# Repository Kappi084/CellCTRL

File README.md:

# CellCTRL
Ist ein modulares System, um ein kleines Produktionssystem aufbauen zu können.

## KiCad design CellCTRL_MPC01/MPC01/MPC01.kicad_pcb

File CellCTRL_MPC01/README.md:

# CellCTRL Electric

Das MPC01 Board wurde für den Manipulator der KTLA ausgelegt.

Aktoren Anschluss:
4x (TMC2009) Stepper Motor
2x Servo Motor

Sensorik:
3x Endschalter (XYZ)

Bus Systeme:
I2C (Für Test Controller im Test Betrieb) (Ausgeführt über SDA und SCL) Nur bei UNO R3 vorhanden
RS485 Kommunikation einzelner Module zu einer Fertigungskette

## 🛠 Skills
Löten, Basic Bauteilkunde, 

## MPC01

#### Usage:
Der MPC01 Controller ist für die Steuerung von 3 Stepper Motoren (TMC2209 Treiber) mit jeweils einem Endschlater designt. Es können über I2C noch weitere Module mitangesteuert werden, wie den MPC-Servo und MPC-Status. Über RS485 sollen mit den anderen Module der Produktionsstraße kommuniziert werden können. (Error Übergabe, Befehle, etc.) Mit der Anbindung von PDNUart, ist es möglich den Motor nach dem Einschalten zu konfigurieren.

#### Features:
3x Steppermotor
3x Endschalter 
1x Notaussignal (Enable_Stepper) (NC)
1x I2C
1x RS485

| Connector | Arduino Pin     | Description                |
| :-------- | :------- | :------------------------- |
| `Endstop Z` | `A0` | NC_Endstop |
| `Endstop Y` | `A1` | NC_Endstop |
| `Endstop X` | `A2` | NC_Endstop |
| `RS485_DE/RE` | `A3` | RS485 |
| `SDA/SCL` | `A4` | I2C |
| `SDA/SCL` | `A5` | I2C |
| `DIR 3` | `D2` | Motor 3 |
| `STEP 3` | `D3` | Motor 3 |
| `DIR 2` | `D4` | Motor 2 |
| `STEP 2` | `D5` | Motor 2 |
| `DIR 1` | `D6` | Motor 1 |
| `STEP 1` | `D7` | Motor 1 |
| `TX` | `D8` | PDNUart StepperMotor |
| `RX` | `D9` | PDNUart StepperMotor |
| `RS485 TX` | `D10` | RS485 |
| `RS485 RX` | `D11` | RS485 |
| `PGOOD` | `D12` | Power OK 5V |
| `Enable` | `D13` | Enable Stepper Motor (Notaus) |

### ⚠️ Notes
Um PDNUART verwenden zu können, müssen mit Jumper bei MS1 und MS2 noch die richtigen Adressen eingestellt werden.

## MPC_Servo

#### Usage:
Der MPC_Servo Controller wird über I2C angesteuert, und kann entweder zwei Servos oder einen Servo und einem Endschalter betrieben werden.

#### Features:
1x Servo
1x Servo/Endschalter

#### Schnittstellenbescreibung:

| Address | Name        | R/W | Description              |
|--------|------------|-----|--------------------------|
| 0x00   | Mode     | R/W   | 0=Dual Servo, 1=Servo+Endstop   |
| 0x01   | Servo1 POS    | R/W | Servo 1 Zielwinkel  (0-180)         |
| 0x02   | Servo2 POS    | R/W | Servo 2 Zielwinkel  (nur Mode 0)         |
| 0x03   | Servo1 CUR   | R   | Servo 1 aktueller Winkel        |
| 0x04   | Servo2 CUR   | R   | Servo 2 aktueller Winkel        |
| 0x05   | Endstop   | R   | Endstop 0=offen, 1=ausgeloest        |
| 0x06   | Home CMD   | W   | 1=Homing starten        |
| 0x07   | Home Status   | R   | 0=idle 1=running 2=done 3=error        |
| 0x08   | Status   | R   | bit0=alive        |
| 0x09   | FW Version   | R   | Firmware-Version        |

## MPC_Status

#### Usage:
Der MPC_Status Controller wird ebenfalls mit I2C gesteuert, und wirkt somit wie der Servo ein "Modul". Mit dem ist es möglich, den jeweiligen Status der Anlage anzuzeigen mithilfe von LEDs.

#### Features:
1x LED Statuslicht

| Color | Status     | Description                |
| :-------- | :------- | :------------------------- |
| Blau leuchtend | Boot | Bei hochfahren der Anlage |
| Blau blinkend | Homing | Beim Homen und Initialisieren der Anlage |
| Grün leuchtend | Ready | Die Anlage steht, aber ist Bereit für Befehle |
| Gelb leuchtend | Auto | Ist im Automatikbetrieb, und steht |
| Gelb blinkend | Manual | Ist im Manuelen Betrieb, und steht |
| Rot leuchtend | Moving | Die Anlage bewegt eine Achse etc. |
| Rot blinkend | EStop | Der Not Aus wurde betätigt, muss Quittiert werden! |
| Rot drehend | Error | Es liegt ein Fehler bei der Anlage an! (Quittierung notwendig) |

#### ⚙️ Configuration I2C_Status

- **I²C Address:** `0x3C`
- **Bus Speed:** Up to 400kHz (Fast Mode)
- **Addressing Mode:** 7-bit

#### 📋 Register Map I2C_Status

| Address | Name        | R/W | Description              |
|--------|------------|-----|--------------------------|
| 0x00   | STATUS     | R   | Device status register   |
| 0x01   | CONTROL    | R/W | Control settings         |
| 0x02   | TEMP_MSB   | R   | Temperature (MSB)        |
| 0x03   | TEMP_LSB   | R   | Temperature (LSB)        |

#### 🔄 Example
```cpp
// example code

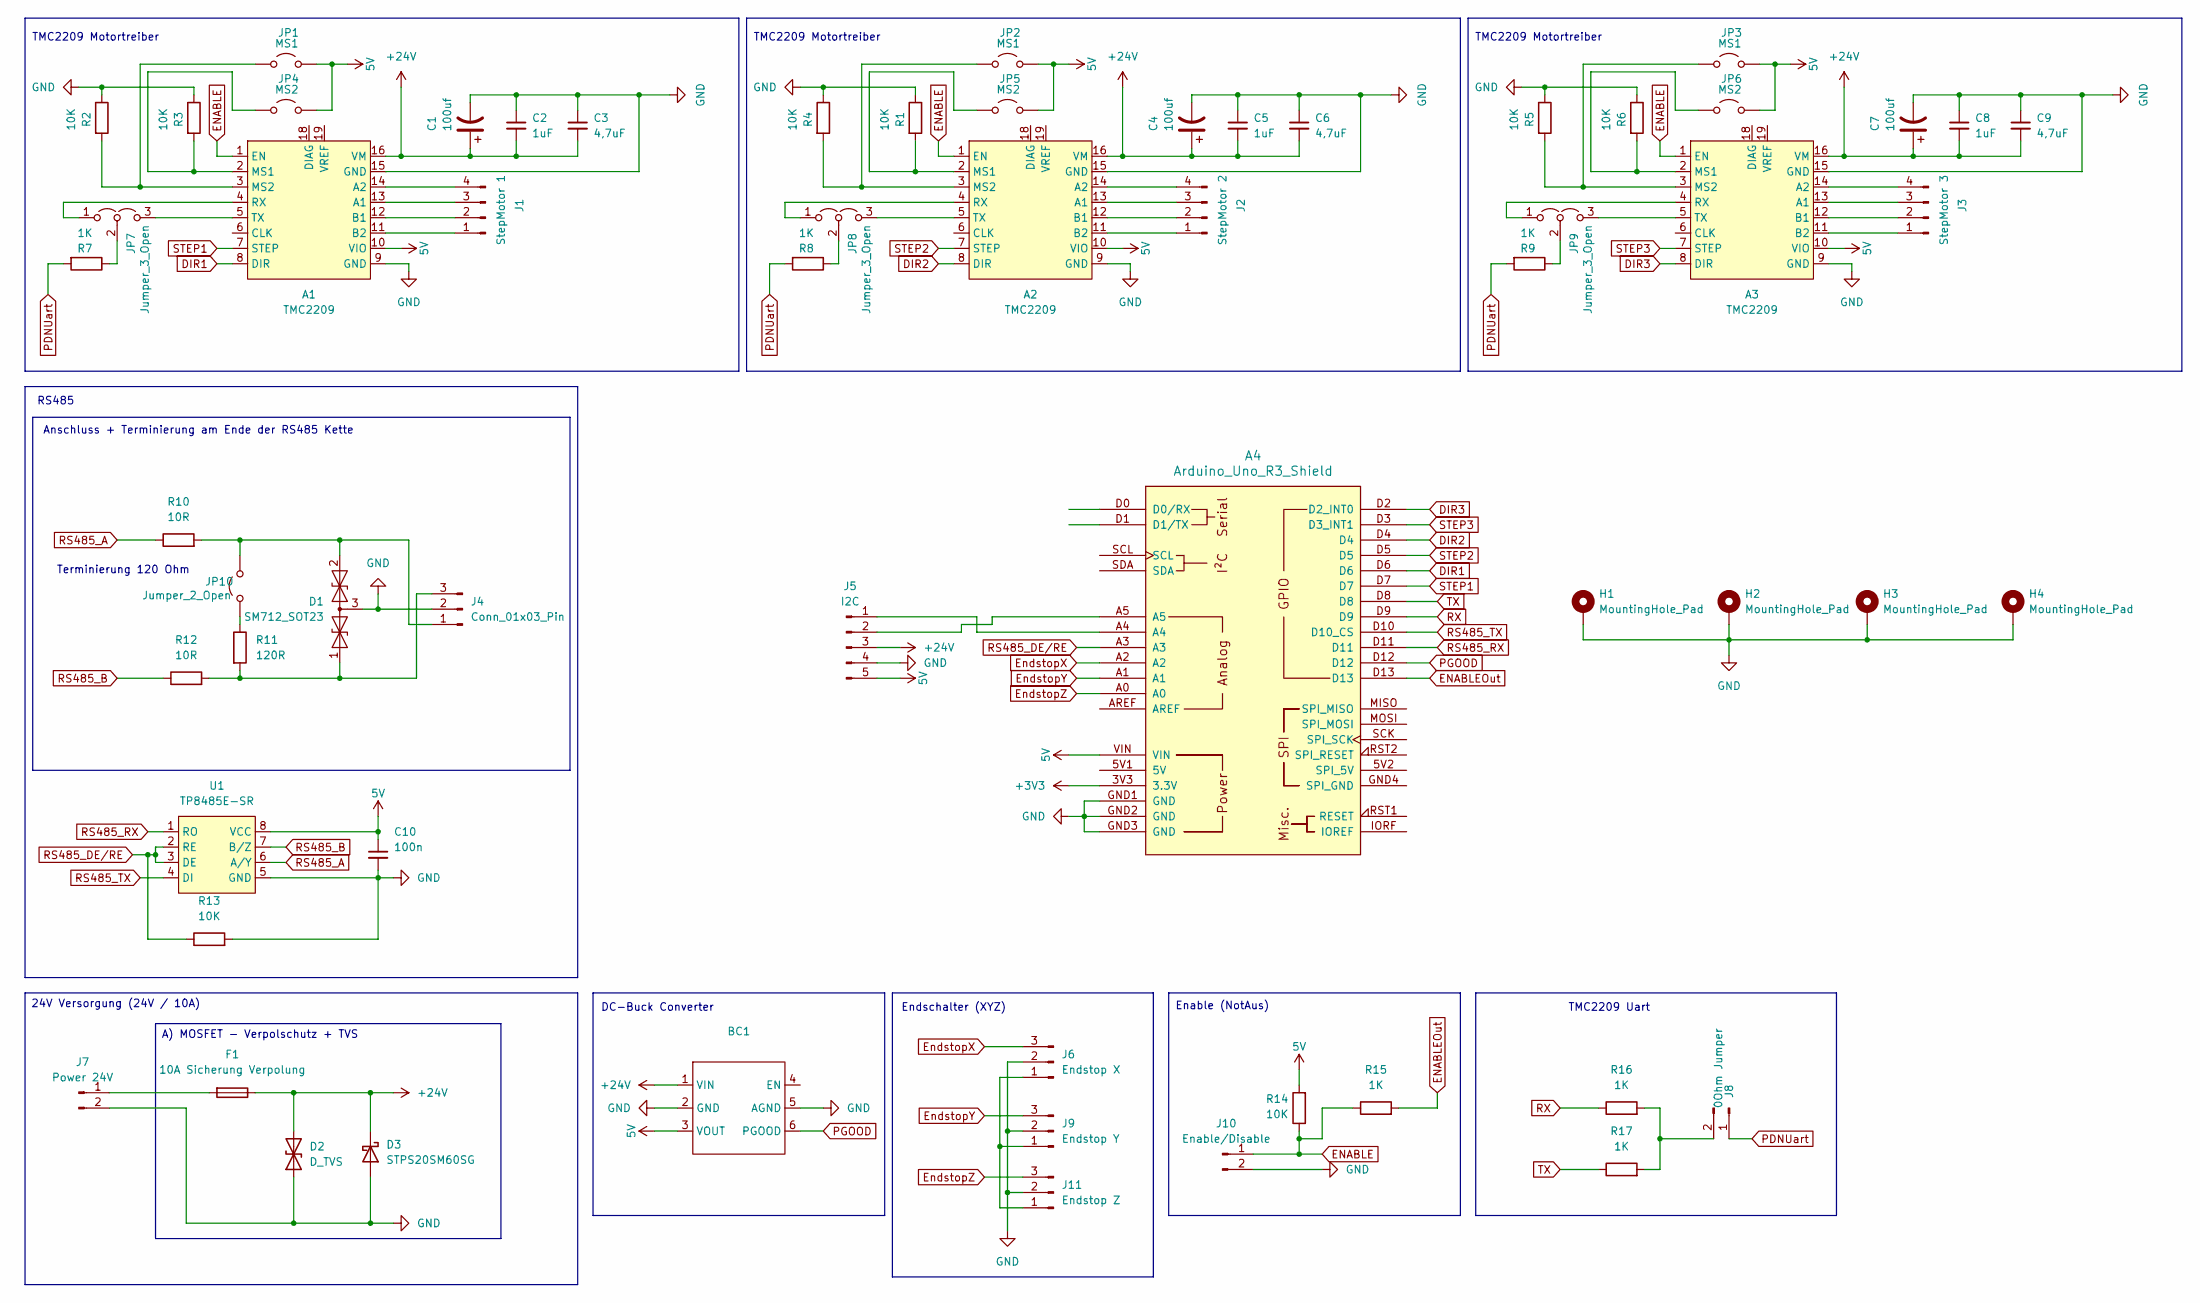
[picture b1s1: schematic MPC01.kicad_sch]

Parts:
A1, A2, A3: TMC2209
A4: Arduino_Uno_R3_Shield
BC1: DC-DC Step Down Buck Converter (6~24V to 5V16A)
C1, C4, C7: 100uf; CP_Elec_6.3x7.7
C2, C5, C8: 1uF; C_0805_2012Metric_Pad1.18x1.45mm_HandSolder; Voltage 1kV; Tolerance 100%
C3, C6, C9: 4,7uF; C_0805_2012Metric_Pad1.18x1.45mm_HandSolder; Voltage 1kV; Tolerance 100%
C10: 100n; C_0805_2012Metric_Pad1.18x1.45mm_HandSolder; Voltage 1kV; Tolerance 100%
D1: SM712_SOT23; SOT-23-3
D2: D_TVS; D_SMB_Handsoldering
D3: STPS20SM60SG; TO-263-2_TabPin2
F1: 10A Sicherung Verpolung; Fuseholder_Littelfuse_Nano2_157x
H1, H2, H3, H4: MountingHole_Pad; MountingHole_2.2mm_M2_DIN965_Pad
J1: StepMotor 1; JST_XH_B4B-XH-A_1x04_P2.50mm_Vertical
J2: StepMotor 2; JST_XH_B4B-XH-A_1x04_P2.50mm_Vertical
J3: StepMotor 3; JST_XH_B4B-XH-A_1x04_P2.50mm_Vertical
J4: Conn_01x03_Pin; PhoenixContact_MSTBA_2,5_3-G-5,08_1x03_P5.08mm_Horizontal
J5: I2C; JST_XH_B5B-XH-A_1x05_P2.50mm_Vertical
J6: Endstop X; JST_XH_B3B-XH-A_1x03_P2.50mm_Vertical
J7: Power 24V; TerminalBlock_WAGO_2601-1102_1x02_P3.50mm_Horizontal
J8: 0Ohm Jumper; PinHeader_1x02_P2.54mm_Vertical
J9: Endstop Y; JST_XH_B3B-XH-A_1x03_P2.50mm_Vertical
J10: Enable/Disable; JST_XH_B2B-XH-A_1x02_P2.50mm_Vertical
J11: Endstop Z; JST_XH_B3B-XH-A_1x03_P2.50mm_Vertical
JP1, JP2, JP3: MS1; PinHeader_1x02_P2.54mm_Vertical
JP4, JP5, JP6: MS2; PinHeader_1x02_P2.54mm_Vertical
JP7, JP8, JP9: Jumper_3_Open; Jumper_3_NO
JP10: Jumper_2_Open; SolderJumper-2_P1.3mm_Open_RoundedPad1.0x1.5mm
R1, R2, R3, R4, R5, R6, R13, R14: 10K; R_0805_2012Metric_Pad1.20x1.40mm_HandSolder
R7, R8, R9, R15, R16, R17: 1K; R_0805_2012Metric_Pad1.20x1.40mm_HandSolder
R10, R12: 10R; R_0805_2012Metric_Pad1.20x1.40mm_HandSolder
R11: 120R; R_0805_2012Metric_Pad1.20x1.40mm_HandSolder
U1: TP8485E-SR; SOP-8_3.76x4.96mm_P1.27mm

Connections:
5V: A1.10 (VIO), A2.10 (VIO), A3.10 (VIO), A4.VIN, BC1.3 (VOUT), C10.1, J5.5, JP1.2 (B), JP2.2 (B), JP3.2 (B), JP4.2 (B), JP5.2 (B), JP6.2 (B), R14.2, U1.8 (VCC)
+3V3: A4.3V3 (3.3V)
+24V: A1.16 (VM), A2.16 (VM), A3.16 (VM), BC1.1 (VIN), C1.1, C2.2, C3.2, C4.1, C5.2, C6.2, C7.1, C8.2, C9.2, D2.2 (A2), D3.1 (K), F1.1, J5.3
DIR1: A1.8 (DIR), A4.D6
DIR2: A2.8 (DIR), A4.D4
DIR3: A3.8 (DIR), A4.D2 (D2_INT0)
ENABLE: A1.1 (EN), A2.1 (EN), A3.1 (EN), J10.1, R14.1, R15.1
ENABLEOut: A4.D13, R15.2
EndstopX: A4.A2, J6.3
EndstopY: A4.A1, J9.3
EndstopZ: A4.A0, J11.3
GND: A1.9 (GND), A1.15 (GND), A2.9 (GND), A2.15 (GND), A3.9 (GND), A3.15 (GND), A4.GND1 (GND), A4.GND2 (GND), A4.GND3 (GND), BC1.2 (GND), BC1.5 (AGND), C1.2, C2.1, C3.1, C4.2, C5.1, C6.1, C7.2, C8.1, C9.1, C10.2, D1.3 (common), D2.1 (A1), D3.2 (A), H1.1, H2.1, H3.1, H4.1, J4.2, J5.4, J6.2, J7.2, J9.2, J10.2, J11.2, R1.1, R2.1, R3.1, R4.1, R5.1, R6.1, R13.2, U1.5 (GND)
unnamed: A1.13 (A1), J1.3
unnamed: A1.14 (A2), J1.4
unnamed: A1.12 (B1), J1.2
unnamed: A1.11 (B2), J1.1
unnamed: A1.2 (MS1), JP4.1 (A), R3.2
unnamed: A1.3 (MS2), JP1.1 (A), R2.2
unnamed: A1.4 (RX), JP7.1 (A)
unnamed: A1.5 (TX), JP7.3 (B)
unnamed: A2.13 (A1), J2.3
unnamed: A2.14 (A2), J2.4
unnamed: A2.12 (B1), J2.2
unnamed: A2.11 (B2), J2.1
unnamed: A2.2 (MS1), JP5.1 (A), R1.2
unnamed: A2.3 (MS2), JP2.1 (A), R4.2
unnamed: A2.4 (RX), JP8.1 (A)
unnamed: A2.5 (TX), JP8.3 (B)
unnamed: A3.13 (A1), J3.3
unnamed: A3.14 (A2), J3.4
unnamed: A3.12 (B1), J3.2
unnamed: A3.11 (B2), J3.1
unnamed: A3.2 (MS1), JP6.1 (A), R6.2
unnamed: A3.3 (MS2), JP3.1 (A), R5.2
unnamed: A3.4 (RX), JP9.1 (A)
unnamed: A3.5 (TX), JP9.3 (B)
unnamed: D1.1 (A1), J4.3, R11.2, R12.2
unnamed: D1.2 (A2), J4.1, JP10.2 (B), R10.2
unnamed: A4.A4, J5.1
unnamed: A4.A5, J5.2
unnamed: F1.2, J7.1
unnamed: J8.2, R16.2, R17.2
unnamed: J6.1, J9.1, J11.1
unnamed: JP7.2 (C), R7.1
unnamed: JP8.2 (C), R8.1
unnamed: JP9.2 (C), R9.1
unnamed: JP10.1 (A), R11.1
PDNUart: J8.1, R7.2, R8.2, R9.2
PGOOD: A4.D12, BC1.6 (PGOOD)
RS485_A: R10.1, U1.6 (A/Y)
RS485_B: R12.1, U1.7 (B/Z)
RS485_DE/RE: A4.A3, R13.1, U1.2 (RE), U1.3 (DE)
RS485_RX: A4.D11, U1.1 (RO)
RS485_TX: A4.D10 (D10_CS), U1.4 (DI)
RX: A4.D9, R16.1
STEP1: A1.7 (STEP), A4.D7
STEP2: A2.7 (STEP), A4.D5
STEP3: A3.7 (STEP), A4.D3 (D3_INT1)
TX: A4.D8, R17.1

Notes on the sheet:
Terminierung 120 Ohm
Enable (NotAus)
TMC2209 Motortreiber
RS485
Endschalter (XYZ)
Anschluss + Terminierung am Ende der RS485 Kette
DC-Buck Converter
TMC2209 Uart
24V Versorgung (24V / 10A)
A) MOSFET - Verpolschutz + TVS

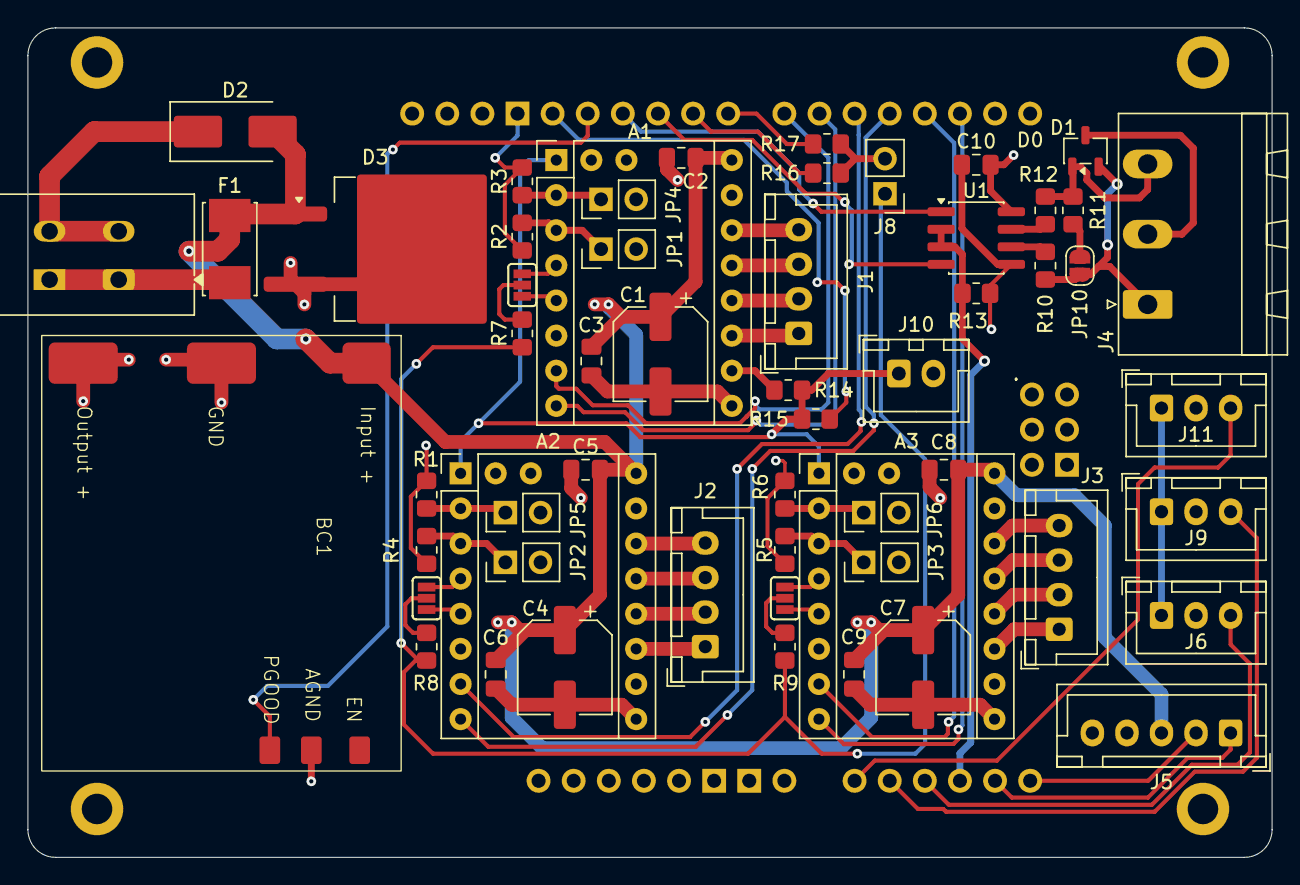
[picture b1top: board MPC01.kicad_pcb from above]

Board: 4 copper layers, 90.0 x 60.0 mm, 62 parts (0 on the bottom side), 58 nets.

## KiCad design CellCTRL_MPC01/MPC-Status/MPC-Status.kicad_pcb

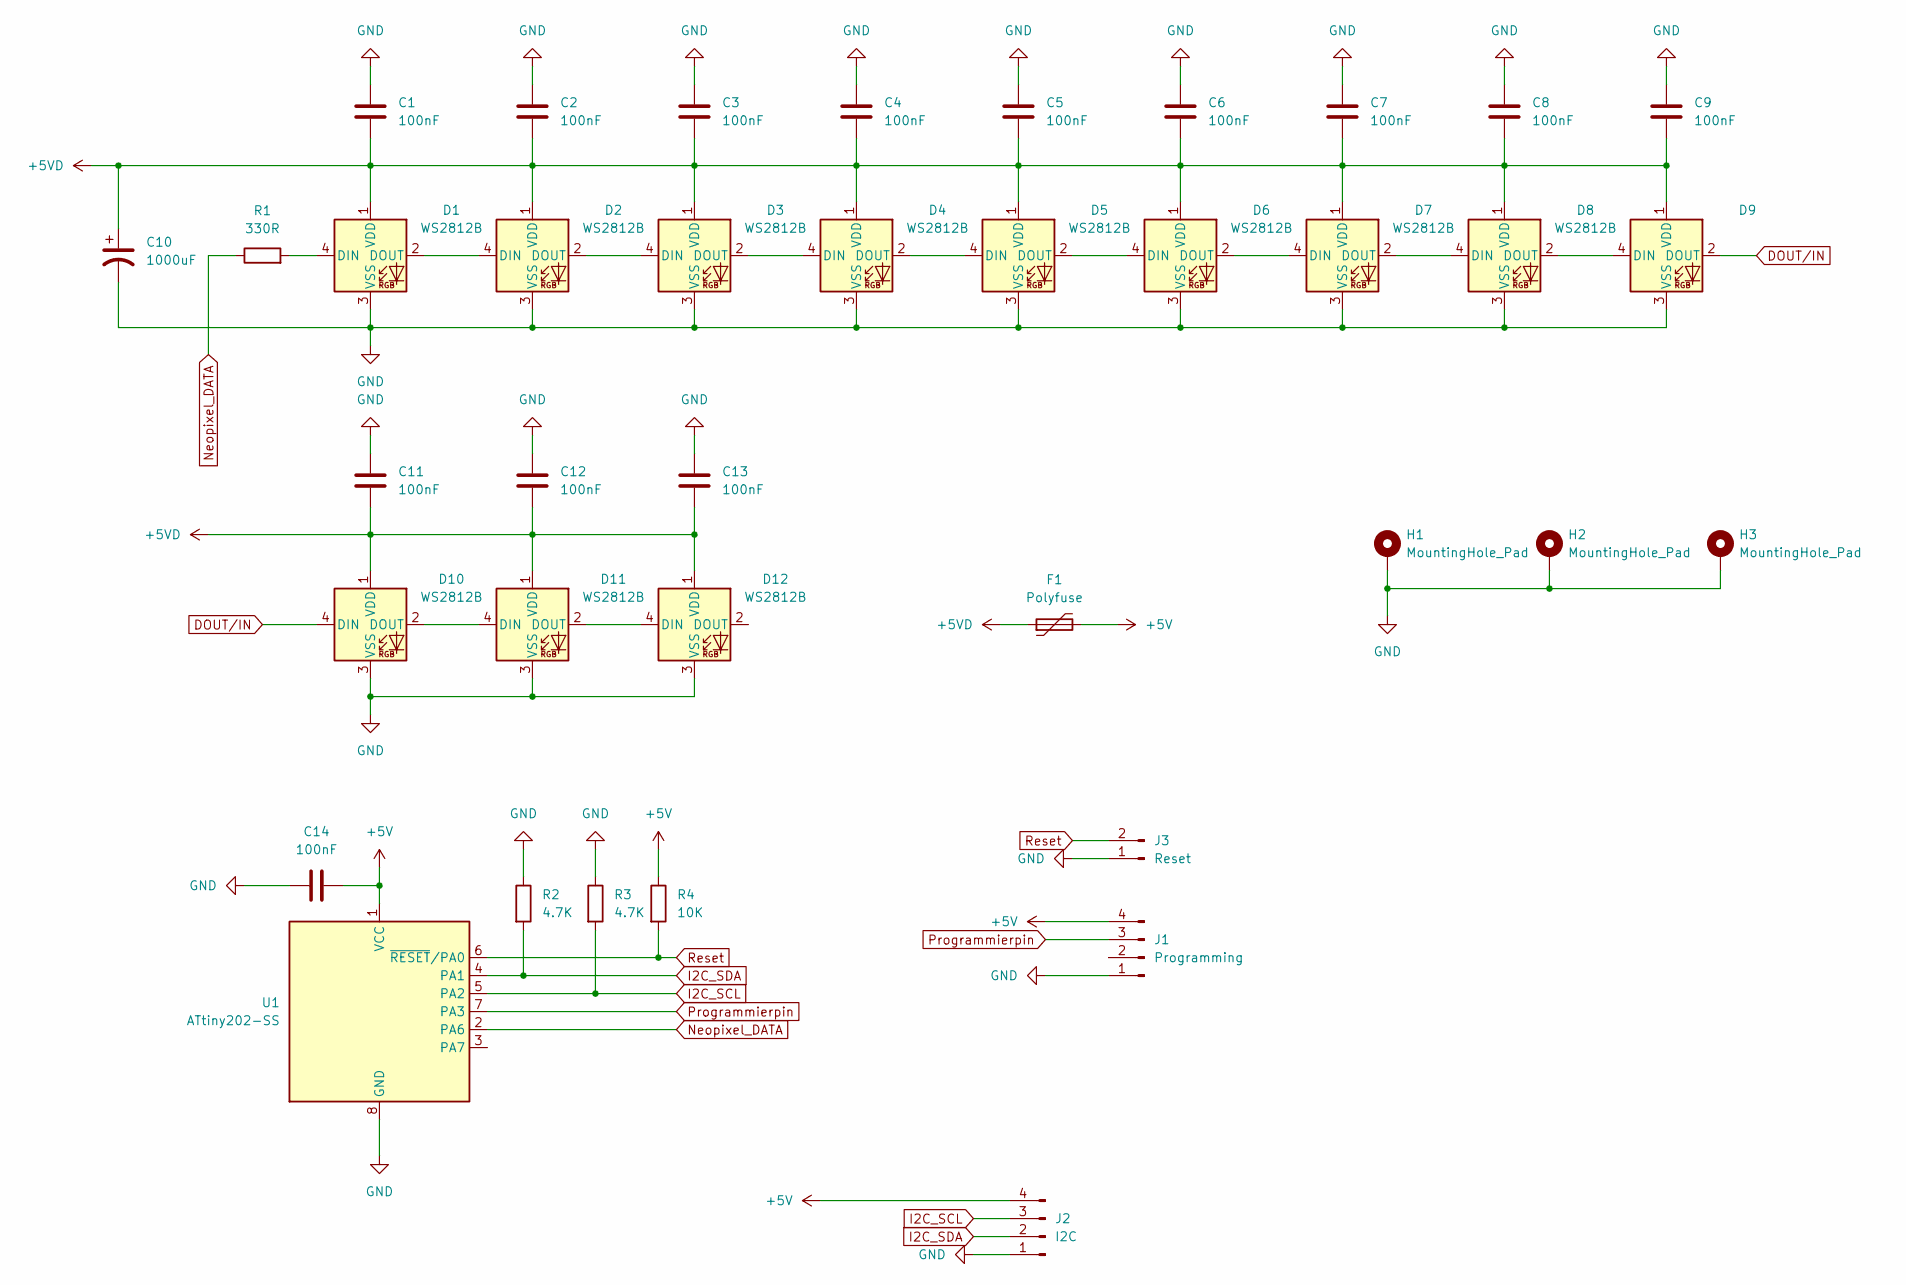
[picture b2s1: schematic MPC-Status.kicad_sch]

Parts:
C1, C2, C3, C4, C5, C6, C7, C8, C9, C11, C12, C13, C14: 100nF; C_0805_2012Metric_Pad1.18x1.45mm_HandSolder
C10: 1000uF; CP_Elec_6.3x5.4
D1, D2, D3, D4, D5, D6, D7, D8, D9, D10, D11, D12: WS2812B; LED_WS2812B_PLCC4_5.0x5.0mm_P3.2mm
F1: Polyfuse; Fuse_0805_2012Metric_Pad1.15x1.40mm_HandSolder
H1, H2, H3: MountingHole_Pad; MountingHole_3.2mm_M3_DIN965_Pad
J1: Programming; PinHeader_1x04_P2.54mm_Vertical
J2: I2C; JST_XH_B4B-XH-A_1x04_P2.50mm_Vertical
J3: Reset; PinHeader_1x02_P2.54mm_Vertical
R1: 330R; R_0805_2012Metric_Pad1.20x1.40mm_HandSolder
R2, R3: 4.7K; R_0805_2012Metric_Pad1.20x1.40mm_HandSolder
R4: 10K; R_0805_2012Metric_Pad1.20x1.40mm_HandSolder
U1: ATtiny202-SS; SOIC-8_3.9x4.9mm_P1.27mm

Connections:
+5V: C14.2, F1.2, J1.4, J2.4, R4.1, U1.1 (VCC)
+5VD: C1.1, C2.1, C3.1, C4.1, C5.1, C6.1, C7.1, C8.1, C9.1, C10.1, C11.1, C12.1, C13.1, D1.1 (VDD), D2.1 (VDD), D3.1 (VDD), D4.1 (VDD), D5.1 (VDD), D6.1 (VDD), D7.1 (VDD), D8.1 (VDD), D9.1 (VDD), D10.1 (VDD), D11.1 (VDD), D12.1 (VDD), F1.1
DOUT/IN: D9.2 (DOUT), D10.4 (DIN)
GND: C1.2, C2.2, C3.2, C4.2, C5.2, C6.2, C7.2, C8.2, C9.2, C10.2, C11.2, C12.2, C13.2, C14.1, D1.3 (VSS), D2.3 (VSS), D3.3 (VSS), D4.3 (VSS), D5.3 (VSS), D6.3 (VSS), D7.3 (VSS), D8.3 (VSS), D9.3 (VSS), D10.3 (VSS), D11.3 (VSS), D12.3 (VSS), H1.1, H2.1, H3.1, J1.1, J2.1, J3.1, R2.1, R3.1, U1.8 (GND)
I2C_SCL: J2.3, R3.2, U1.5 (PA2)
I2C_SDA: J2.2, R2.2, U1.4 (PA1)
Neopixel_DATA: R1.1, U1.2 (PA6)
unnamed: D1.4 (DIN), R1.2
unnamed: D1.2 (DOUT), D2.4 (DIN)
unnamed: D2.2 (DOUT), D3.4 (DIN)
unnamed: D3.2 (DOUT), D4.4 (DIN)
unnamed: D4.2 (DOUT), D5.4 (DIN)
unnamed: D5.2 (DOUT), D6.4 (DIN)
unnamed: D6.2 (DOUT), D7.4 (DIN)
unnamed: D7.2 (DOUT), D8.4 (DIN)
unnamed: D8.2 (DOUT), D9.4 (DIN)
unnamed: D10.2 (DOUT), D11.4 (DIN)
unnamed: D11.2 (DOUT), D12.4 (DIN)
Programmierpin: J1.3, U1.7 (PA3)
Reset: J3.2, R4.2, U1.6 (~RESET/PA0)

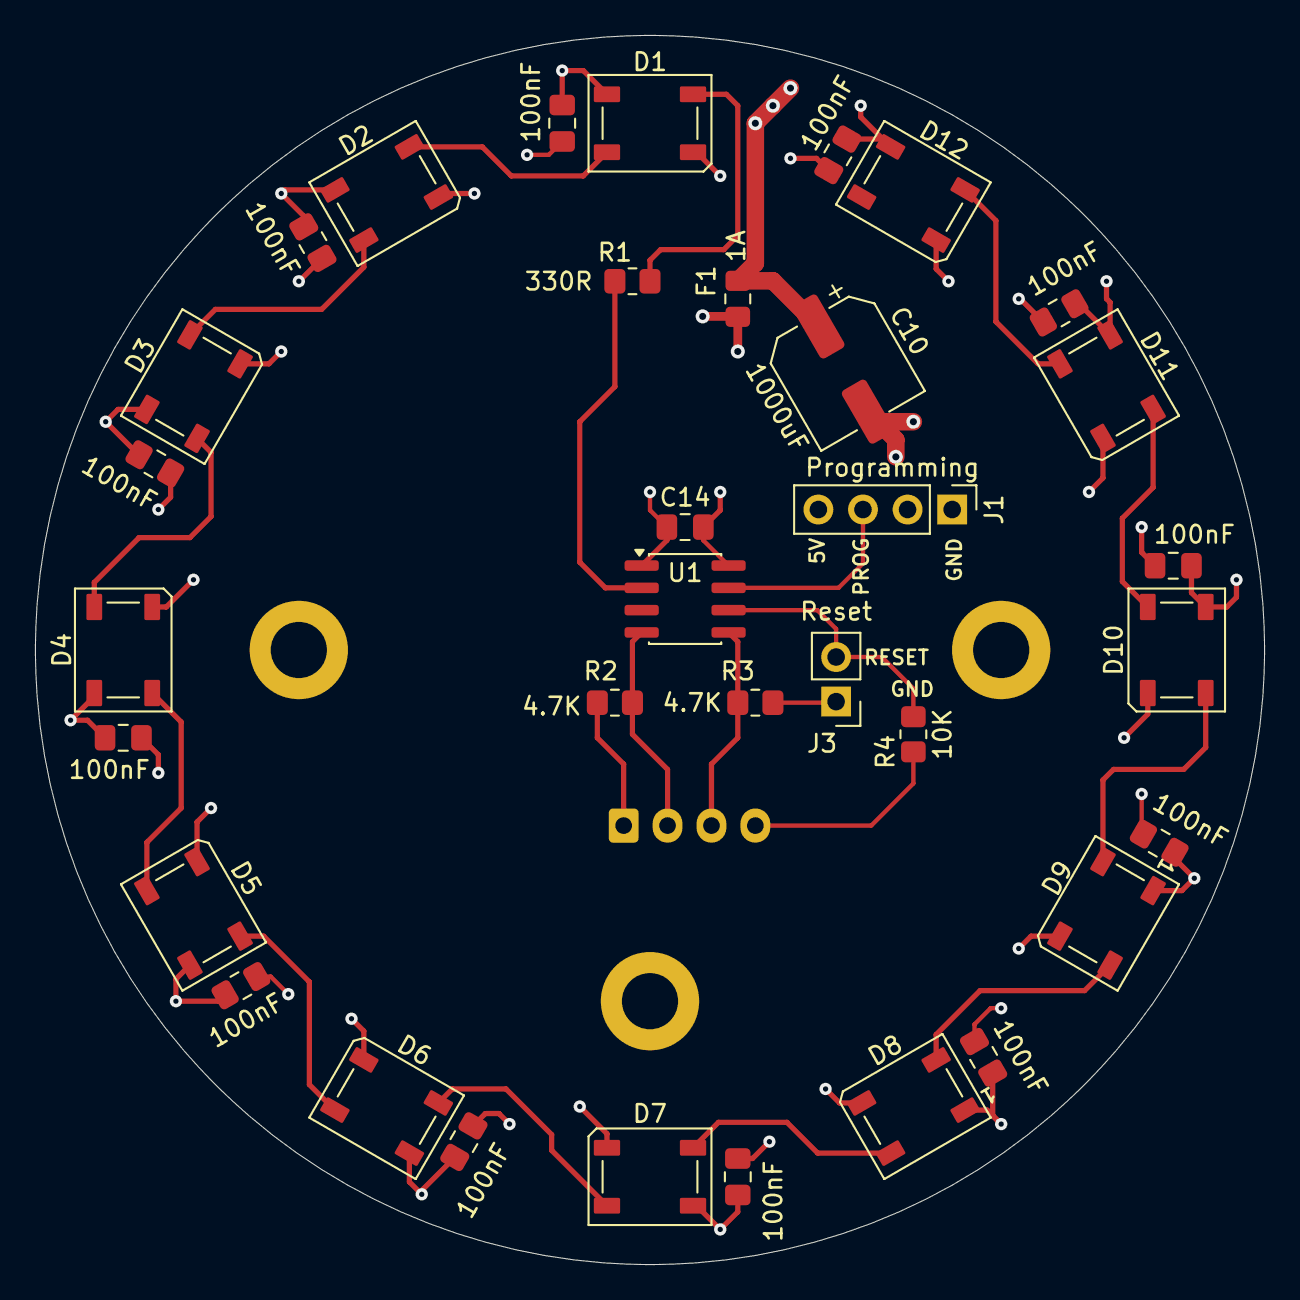
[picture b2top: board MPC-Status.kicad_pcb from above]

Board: 4 copper layers, 70.0 x 70.0 mm, 38 parts (1 on the bottom side), 20 nets.

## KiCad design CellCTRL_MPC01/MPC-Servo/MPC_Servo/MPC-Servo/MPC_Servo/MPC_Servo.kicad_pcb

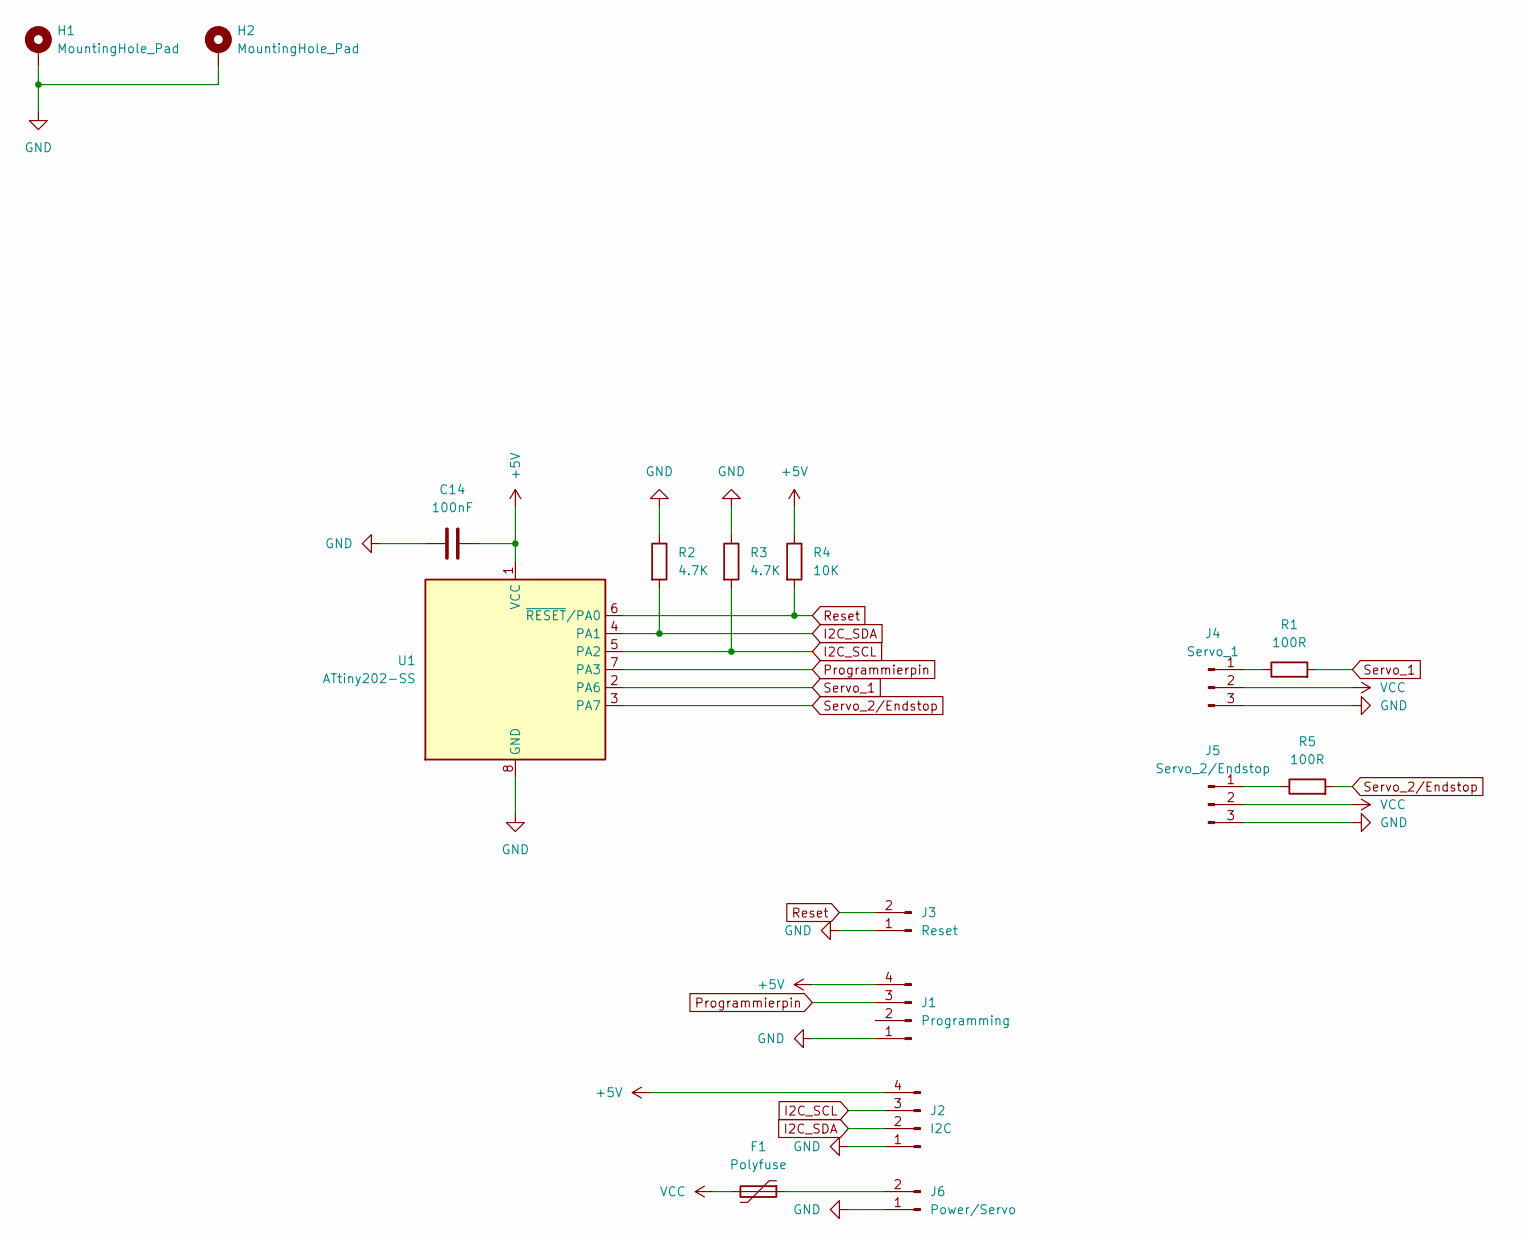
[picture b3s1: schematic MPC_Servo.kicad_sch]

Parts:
C14: 100nF; C_0805_2012Metric_Pad1.18x1.45mm_HandSolder
F1: Polyfuse; Fuse_0805_2012Metric_Pad1.15x1.40mm_HandSolder
H1, H2: MountingHole_Pad; MountingHole_3.2mm_M3_DIN965_Pad
J1: Programming; PinHeader_1x04_P2.54mm_Vertical
J2: I2C; JST_EH_B4B-EH-A_1x04_P2.50mm_Vertical
J3: Reset; PinHeader_1x02_P2.54mm_Vertical
J4: Servo_1; JST_PH_B3B-PH-K_1x03_P2.00mm_Vertical
J5: Servo_2/Endstop; JST_PH_B3B-PH-K_1x03_P2.00mm_Vertical
J6: Power/Servo; PinHeader_1x02_P2.54mm_Vertical
R1, R5: 100R; R_0805_2012Metric_Pad1.20x1.40mm_HandSolder
R2, R3: 4.7K; R_0805_2012Metric_Pad1.20x1.40mm_HandSolder
R4: 10K; R_0805_2012Metric_Pad1.20x1.40mm_HandSolder
U1: ATtiny202-SS; SOIC-8_3.9x4.9mm_P1.27mm

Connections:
+5V: C14.2, J1.4, J2.4, R4.1, U1.1 (VCC)
GND: C14.1, H1.1, H2.1, J1.1, J2.1, J3.1, J4.3, J5.3, J6.1, R2.1, R3.1, U1.8 (GND)
I2C_SCL: J2.3, R3.2, U1.5 (PA2)
I2C_SDA: J2.2, R2.2, U1.4 (PA1)
unnamed: J4.1, R1.1
unnamed: J5.1, R5.1
unnamed: F1.1, J6.2
Programmierpin: J1.3, U1.7 (PA3)
Reset: J3.2, R4.2, U1.6 (~RESET/PA0)
Servo_1: R1.2, U1.2 (PA6)
Servo_2/Endstop: R5.2, U1.3 (PA7)
VCC: F1.2, J4.2, J5.2

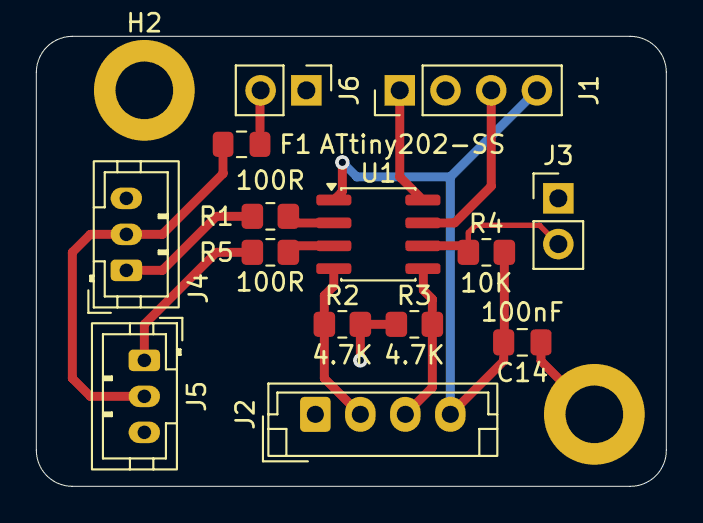
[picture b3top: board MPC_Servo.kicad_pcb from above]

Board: 2 copper layers, 35.0 x 25.0 mm, 16 parts (0 on the bottom side), 12 nets.

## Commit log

2026-02-21 Upload CellCTRL_MPC01
    Upload of all the KICAD Files for the MPC01 Module. It's an V0.1 Version. So it's not tested yet!
2026-02-22 Silkscreen Add Files
    Hinzufügen der Beschriftungen auf dem Silkscreen FRont and Back
2026-02-24 Upload MPC-Status
2026-02-25 Update der PCBs
    MPC01: Update der Schematics (Lötbrücken anstatt von Steckbrücken bei MSN und generell Brücken bei PDNUart)
    MPC-Status: Fertigstellen des PCBs
2026-02-26 Add CellCTRL_MPC-01 as submodule
2026-03-07 New schematics
    Many Changes:)
2026-03-08 Update MPC01
    MPC01 update
2026-03-09 Mounting Hole adds
2026-03-10 Maße
2026-03-13 Adding MPC_Servo
2026-03-18 ready
    fertig
2026-03-23 Fertig V0.1_Servo
2026-03-23 Fertig V0.1_Servo
    Erneutes Hochladen um den Zwischen Ordner zu löschen
2026-03-23 Fertig V0.1_Status
2026-03-23 Fertig V0.1_MPC01
2026-03-23 Adding Schematic.pdf, Adding Fotos 3d model, Adding Step files
2026-03-23 Adding Files
2026-03-23 Enhance README with MPC01 details and features
    Added detailed usage instructions, features, and connector information for the MPC01 controller.
2026-03-23 Enhance README with detailed controller information
    Updated README.md to include additional features and usage details for MPC01, MPC_Servo, and MPC_Status controllers, along with configuration and register map information.
2026-03-23 Enhance README with MPC01 details and examples
    Updated README.md to include additional details about the MPC01 board, its usage, features, and configuration.
2026-04-04 Adding 3d Models
